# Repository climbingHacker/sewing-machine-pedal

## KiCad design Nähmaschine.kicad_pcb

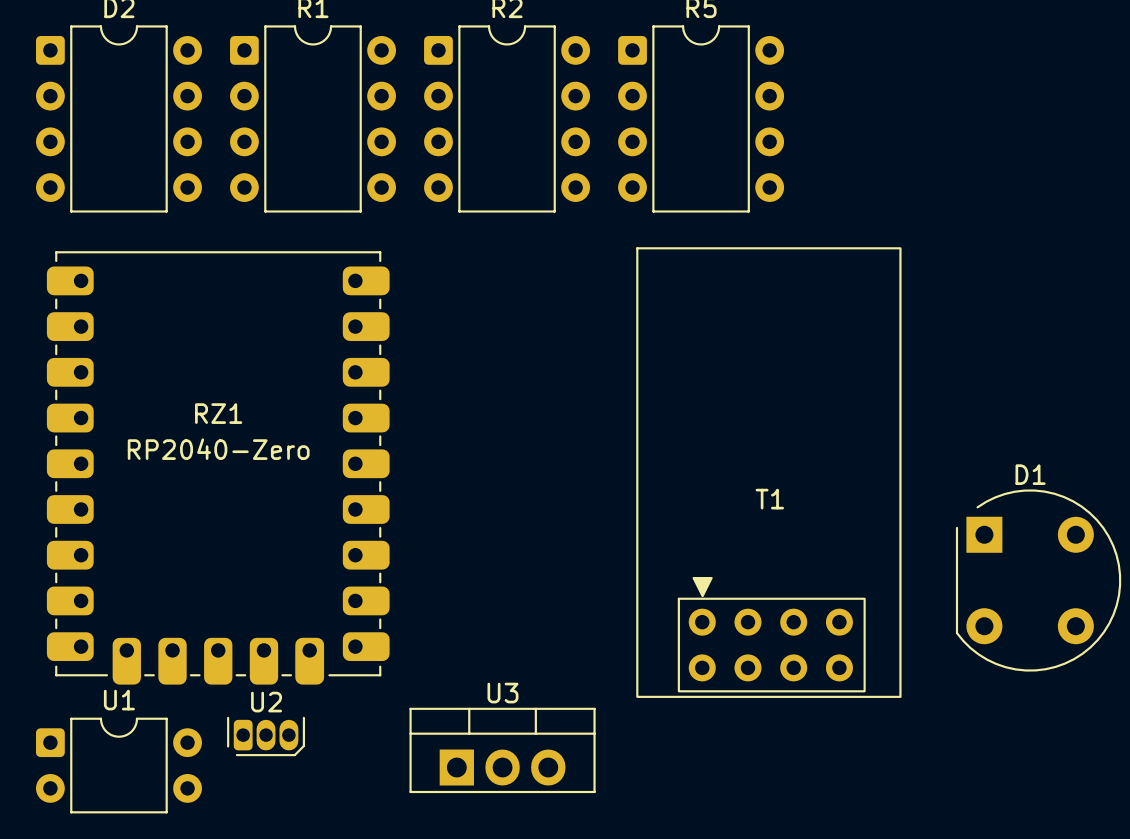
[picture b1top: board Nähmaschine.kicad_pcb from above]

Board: 2 copper layers, 10 parts (0 on the bottom side), 12 nets, no tracks yet.

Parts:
D1: D_Bridge_+AA-; Diode_Bridge_Round_D9.8mm
D2: Generic_Triac_A1A2G; DIP-8_W7.62mm
R1: 220R; DIP-8_W7.62mm
R2: 20K; DIP-8_W7.62mm
R5: 10K; DIP-8_W7.62mm
RZ1: RP2040-Zero
T1: Transformer_1P_1S; ESP-01
U1: PC817; DIP-4_W7.62mm
U2: AH49E; TO-92S
U3: L7805; TO-220-3_Vertical

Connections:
220V: D2.2 (A2), T1.1 (AA)
+5V: RZ1.22 (5V), U1.4, U3.3 (OUT)
GND: D1.4 (-), R1.1, R2.1, RZ1.21 (GND), T1.2 (AB), U2.2 (GND), U3.2 (GND)
unnamed: D1.1 (+), U1.1, U3.1 (IN)
unnamed: D2.3 (G), RZ1.1 (GP1)
unnamed: R1.2, U1.2
unnamed: R5.1, U1.3
unnamed: RZ1.20 (3V3), U2.1 (V_{CC})
unnamed: R2.2, R5.2
unnamed: RZ1.19 (GP29), U2.3 (V_{OUT})
unnamed: D1.3, T1.3 (SA)
unnamed: D1.2, T1.4 (SB)
